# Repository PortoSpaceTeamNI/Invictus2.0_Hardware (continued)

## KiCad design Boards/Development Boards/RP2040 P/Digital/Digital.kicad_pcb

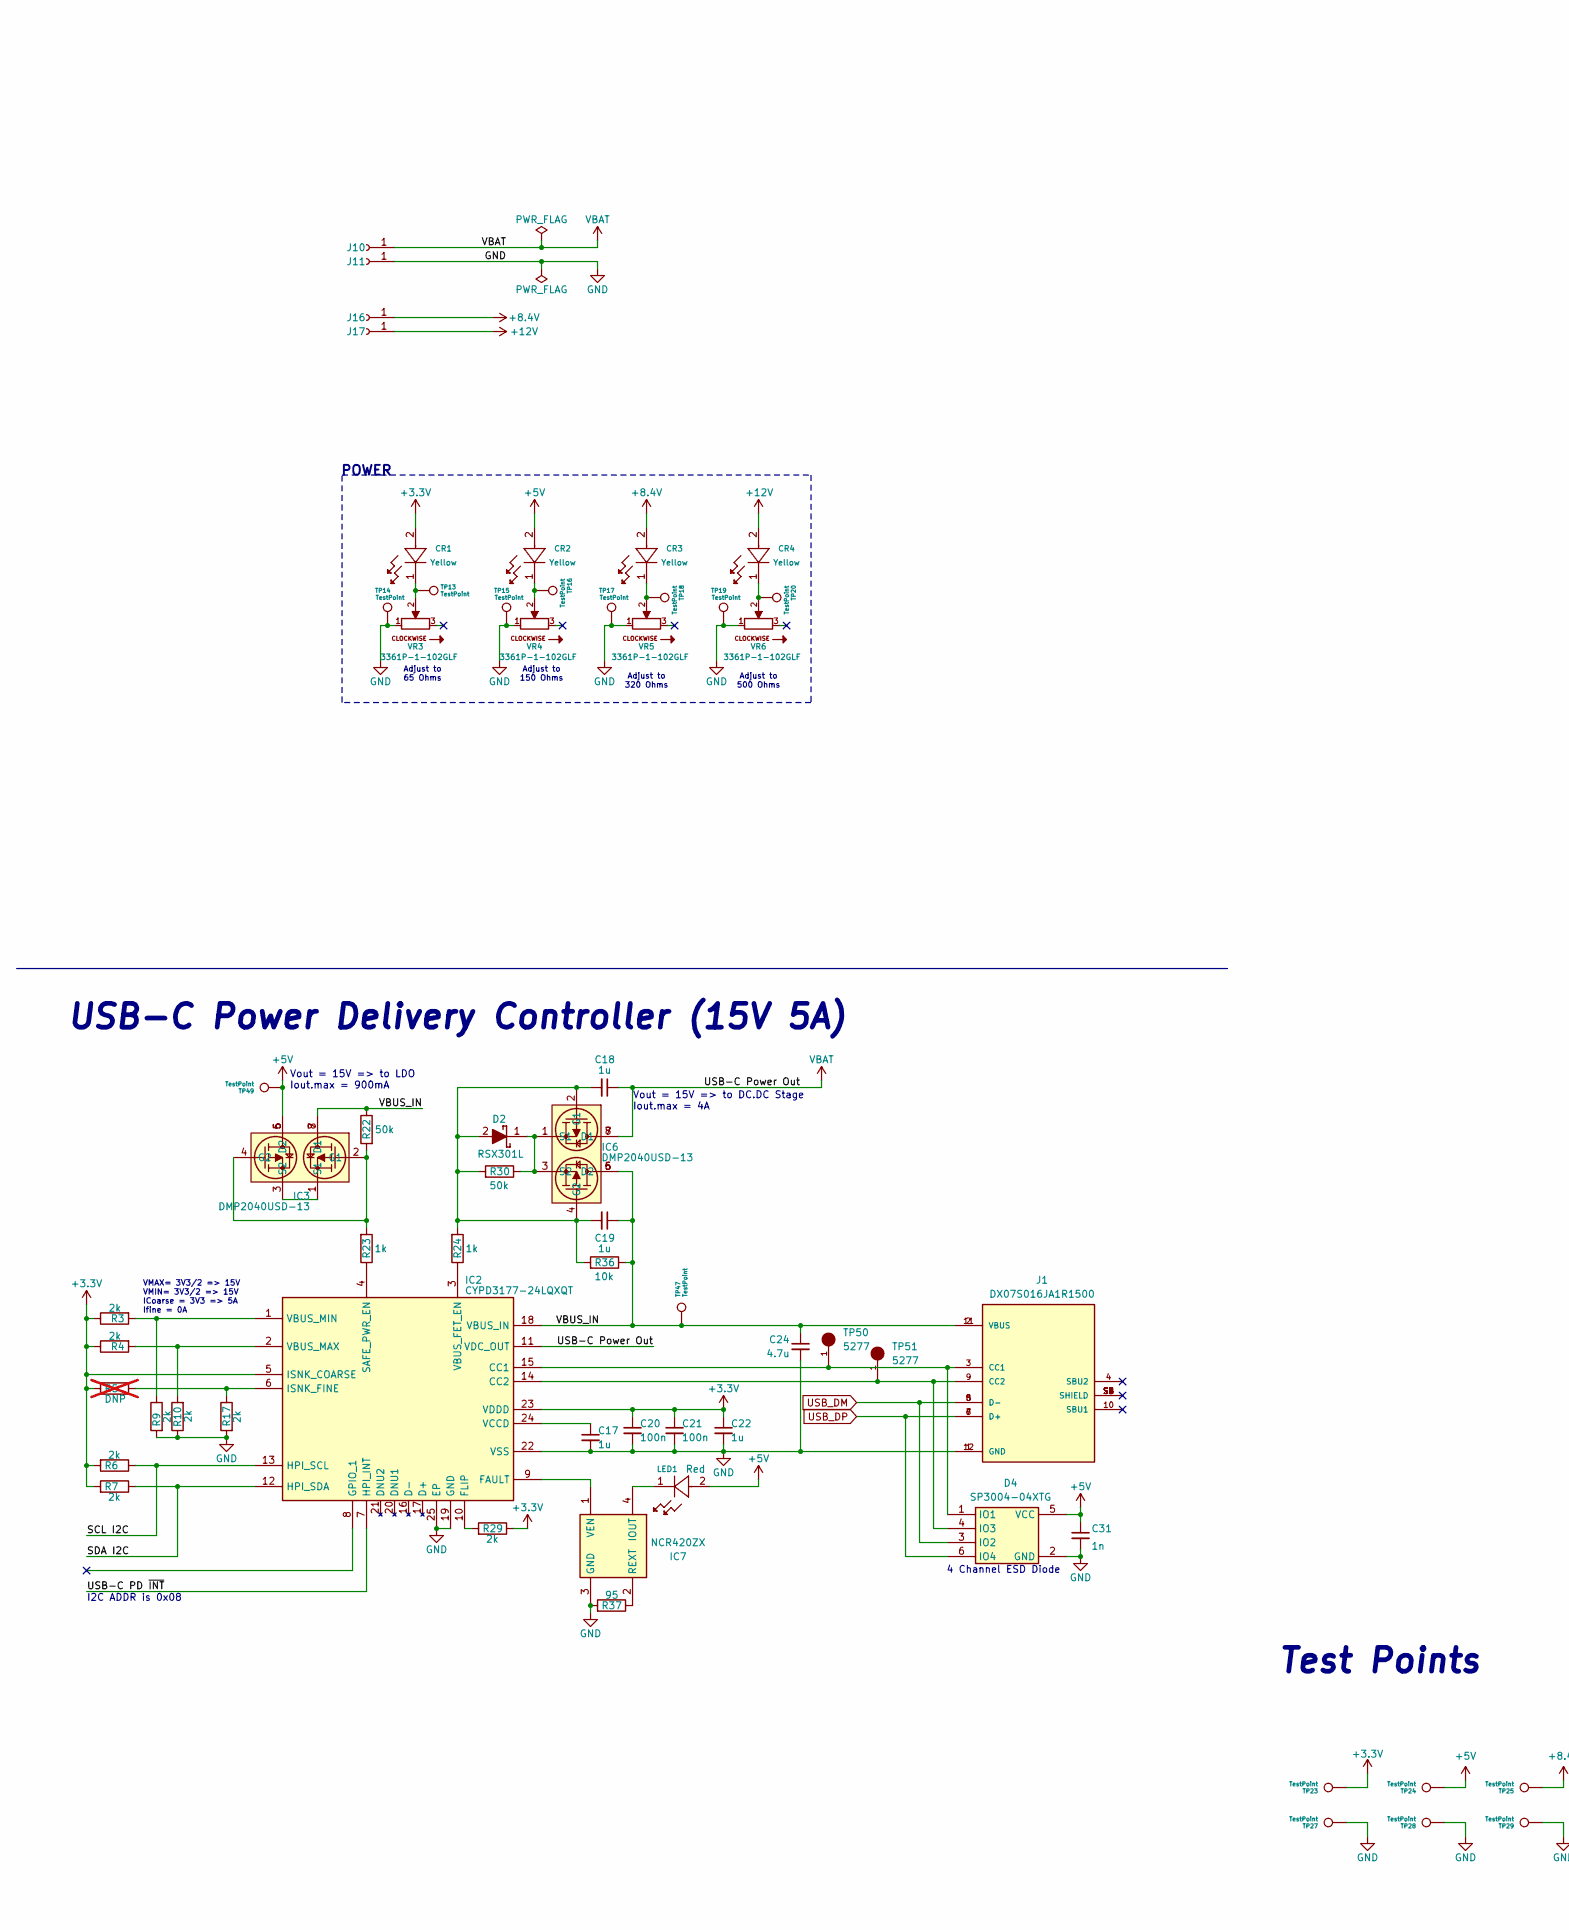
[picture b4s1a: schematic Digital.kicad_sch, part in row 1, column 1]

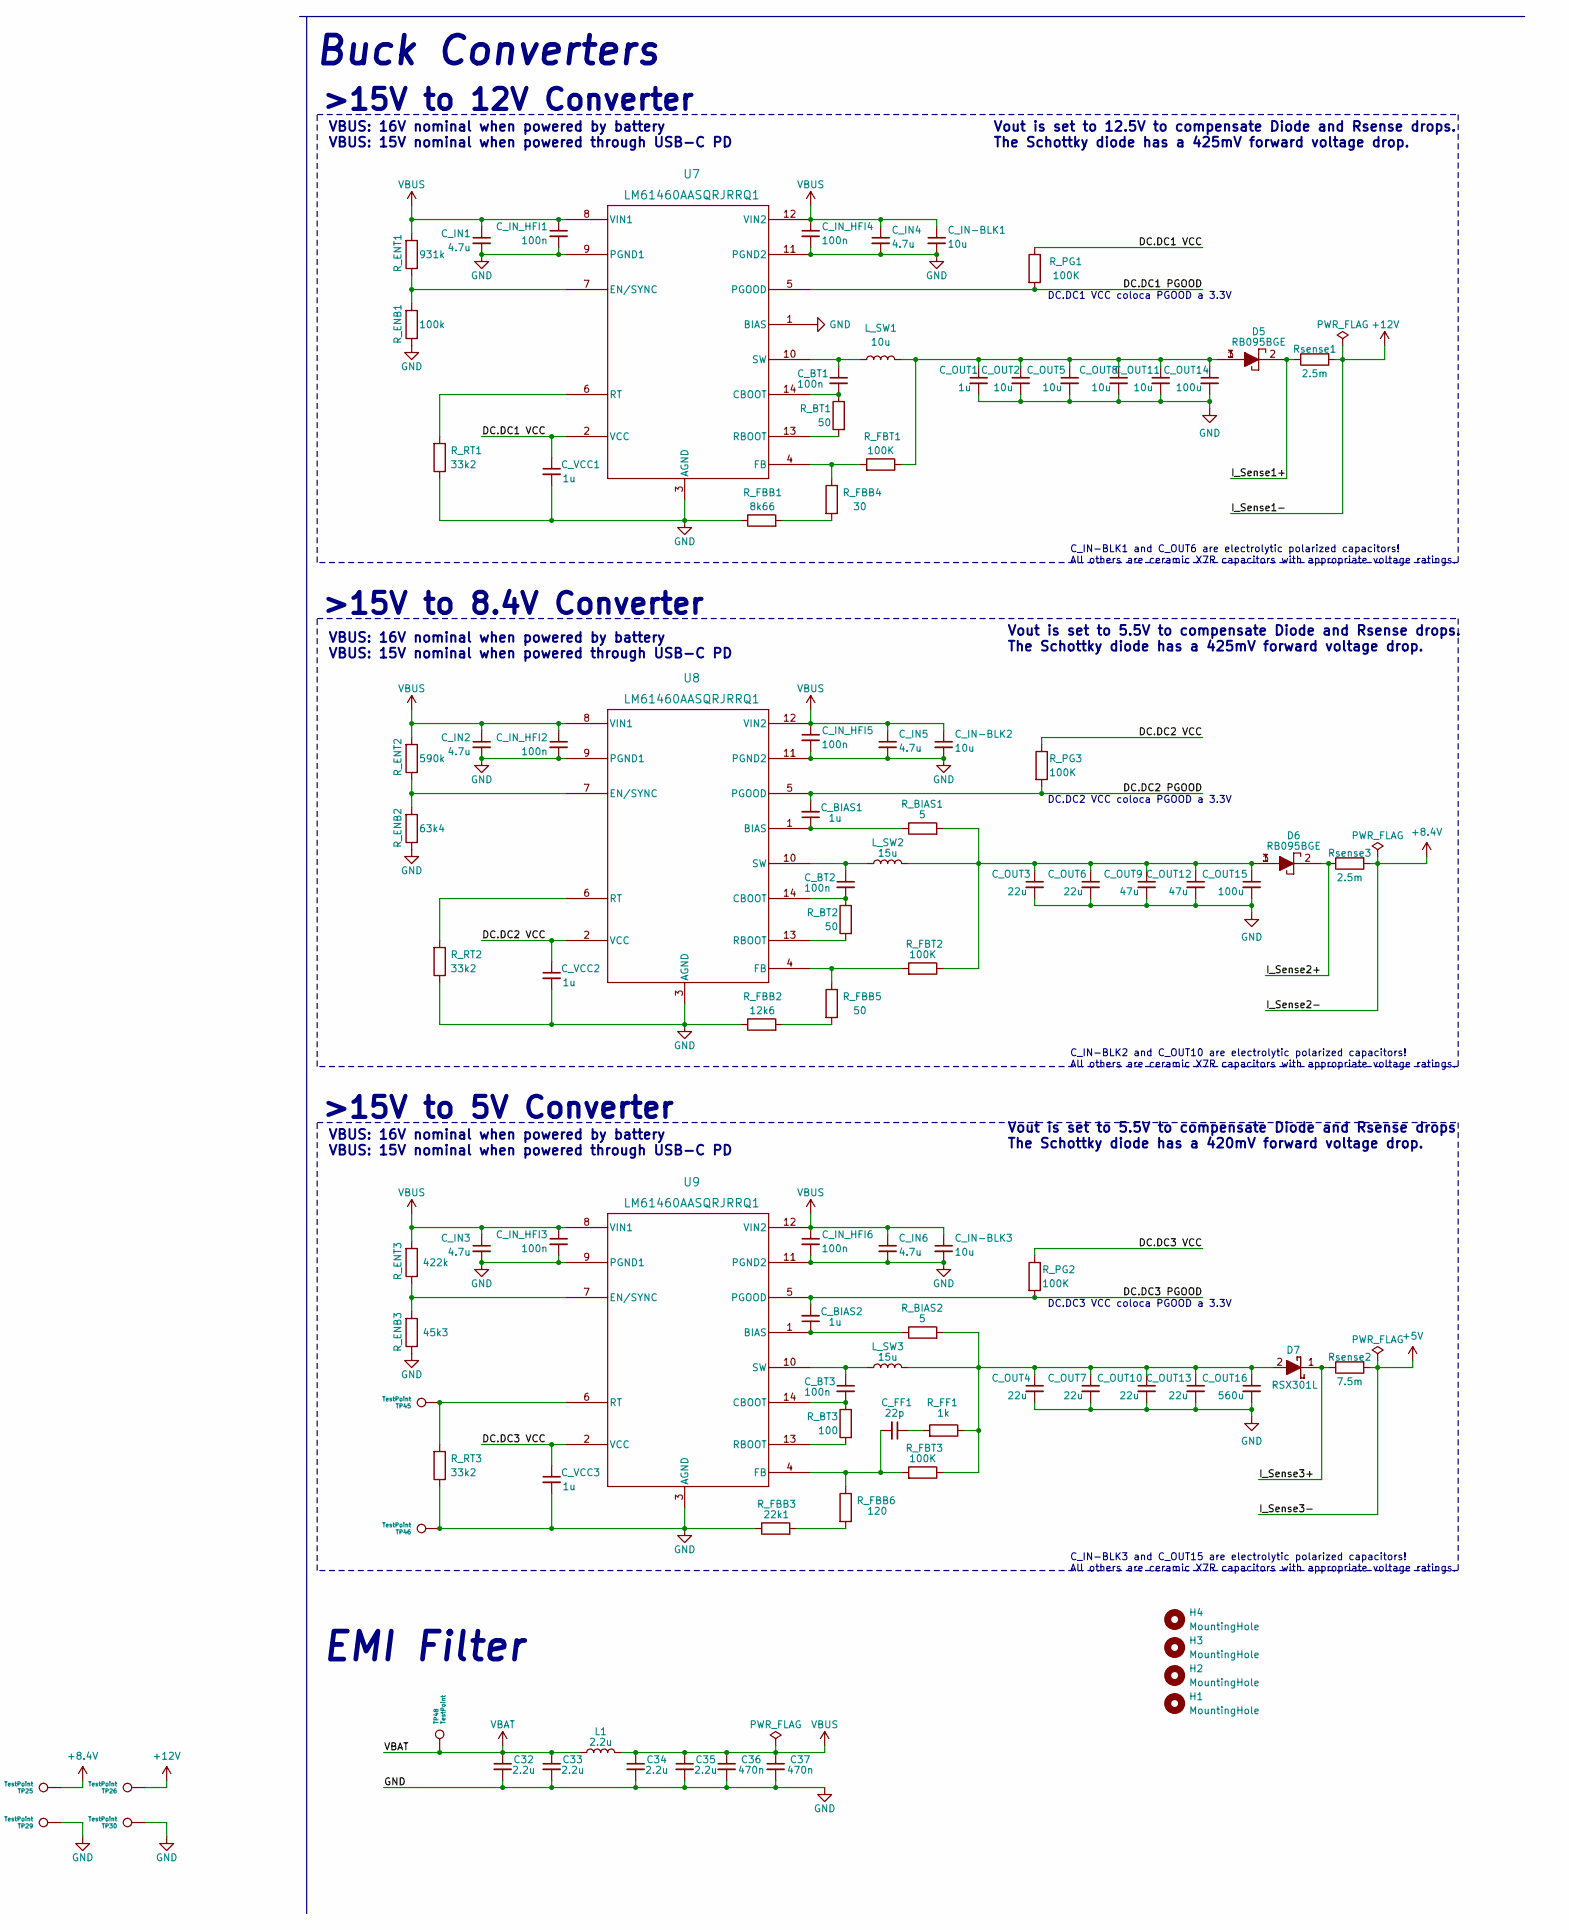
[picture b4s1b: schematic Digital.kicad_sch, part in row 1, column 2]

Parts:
C17, C18, C19, C22: 1u; Capacitor_0603
C20, C21: 100n; Capacitor_0402
C24: 4.7u; Capacitor_1206
C31: 1n; Capacitor_0402
C32, C33, C34, C35: 2.2u; Capacitor_0402
C36, C37: 470n; Capacitor_0402
CR1, CR2, CR3, CR4: VLMY1300-GS08; LEDC1608X100N
C_BIAS1, C_BIAS2: 1u; Capacitor_0603
C_BT1, C_BT2, C_BT3: 100n; Capacitor_0402
C_FF1: 22p; Capacitor_0402
C_IN1, C_IN2, C_IN3, C_IN4, C_IN5, C_IN6: 4.7u; Capacitor_1206
C_IN-BLK1, C_IN-BLK2, C_IN-BLK3: 10u; Capacitor_4mm
C_IN_HFI1, C_IN_HFI2, C_IN_HFI3, C_IN_HFI4, C_IN_HFI5, C_IN_HFI6: 100n; Capacitor_0402
C_OUT1: 1u; Capacitor_0603
C_OUT2, C_OUT5, C_OUT8, C_OUT11: 10u; Capacitor_0805
C_OUT3, C_OUT4, C_OUT6, C_OUT7, C_OUT10, C_OUT13: 22u; Capacitor_0805
C_OUT9, C_OUT12: 47u; Capacitor_0805
C_OUT14: 100u; Capacitor_6mm
C_OUT15: 100u; Capacitor_8mm
C_OUT16: 560u; Capacitor_8mm
C_VCC1, C_VCC2, C_VCC3: 1u; Capacitor_0603
D2, D7: RSX301L; DIOM5026X220N; Mouser Part Number 755-RSX301L-30DDTE25
D4: SP3004-04XTG; SOT563_LTF; Mouser Part Number 576-SP3004-04XTG
D5, D6: RB095BGE; RD3P175SNFRATL; Mouser Part Number 755-RB095BGE-30TL
H1, H2, H3, H4: MountingHole; MountingHole_3.2mm_M3_ISO7380_Pad_TopBottom
IC2: CYPD3177-24LQXQT; QFN50P400X400X60-25N-D; Mouser Part Number 727-CYPD3177-24LQXQT
IC3, IC6: DMP2040USD-13; SOIC127P600X175-8N; Mouser Part Number 621-DMP2040USD-13
IC7: NCR420ZX; SOT230P700X180-4N; Mouser Part Number 771-NCR420ZX
J1: DX07S016JA1R1500; JAE_DX07S016JA1R1500; PARTREV 1
J10, J11, J16, J17: Conn_01x01_Socket; Pico_01pin
L1: 2.2u; Inductor_10.1x10
LED1: VLMS1500-GS08; LED_00-GS08_VIS_RED
L_SW1: 10u; Inductor_11.5x10
L_SW2, L_SW3: 15u; Inductor_10.1x10
R3, R4, R6, R7, R9, R10, R17, R29: 2k; RES_0402
R5: DNP; RES_0402; not fitted
R22, R30: 50k; RES_0402
R23, R24: 1k; RES_0402
R36: 10k; RES_0402
R37: 95; RES_0402
R_BIAS1, R_BIAS2: 5; RES_0402
R_BT1, R_BT2: 50; RES_0402
R_BT3: 100; RES_0402
R_ENB1: 100k; RES_0603
R_ENB2: 63k4; RES_0402
R_ENB3: 45k3; RES_0402
R_ENT1: 931k; RES_0603
R_ENT2: 590k; RES_0402
R_ENT3: 422k; RES_0402
R_FBB1: 8k66; RES_0603
R_FBB2: 12k6; RES_0603
R_FBB3: 22k1; RES_0603
R_FBB4: 30; RES_0603
R_FBB5: 50; RES_0603
R_FBB6: 120; RES_0603
R_FBT1, R_FBT2, R_FBT3: 100K; RES_0603
R_FF1: 1k; RES_0402
R_PG1, R_PG2, R_PG3: 100K; RES_0603
R_RT1, R_RT2, R_RT3: 33k2; RES_0603
Rsense1, Rsense3: 2.5m; RES_0805
Rsense2: 7.5m; RES_WSLP2512
TP13, TP14, TP15, TP16, TP17, TP18, TP19, TP20, TP23, TP24, TP25, TP26, TP27, TP28, TP29, TP30: TestPoint; TestPoint_Pad_2.0x2.0mm
TP45, TP46, TP47, TP48, TP49: TestPoint; KEYSTONE_5277
TP50, TP51: 5277; KEYSTONE_5277
U7, U8, U9: LM61460AASQRJRRQ1; VQFN-HR14_RJR_TEX
VR3, VR4, VR5, VR6: 3361P-1-102GLF; TRIM_3361P-1-102GLF; PARTREV 08/19

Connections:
+3.3V: C20.1, C21.1, C22.1, CR1.2, IC2.5 (ISNK_COARSE), IC2.23 (VDDD), R3.1, R4.1, R5.2, R6.2, R7.2, R29.1, TP23.1; also elsewhere on the board
+5V: C31.1, CR2.2, D4.5 (VCC), IC3.5 (D2), IC3.6 (D2), LED1.2, Rsense2.2, TP24.1, TP49.1; also elsewhere on the board
+8.4V: CR3.2, J16.1, Rsense3.2, TP25.1
+12V: CR4.2, J17.1, Rsense1.2, TP26.1
/DC.DC1 PGOOD: R_PG1.2, U7.5 (PGOOD)
/DC.DC1 VCC: C_VCC1.1, R_PG1.1, U7.2 (VCC)
/DC.DC2 PGOOD: C_BIAS1.2, R_PG3.2, U8.5 (PGOOD)
/DC.DC2 VCC: C_VCC2.1, R_PG3.1, U8.2 (VCC)
/DC.DC3 PGOOD: C_BIAS2.2, R_PG2.2, U9.5 (PGOOD)
/DC.DC3 VCC: C_VCC3.1, R_PG2.1, U9.2 (VCC)
/I_Sense1+: D5.2, Rsense1.1
/I_Sense2+: D6.2, Rsense3.1
/I_Sense3+: D7.1 (K), Rsense2.1; also elsewhere on the board
/SCL I2C: IC2.13 (HPI_SCL), R6.1
/SDA I2C: IC2.12 (HPI_SDA), R7.1
/USB-C PD ~INT: IC2.7 (HPI_INT)
/VBUS_IN: C19.1, C24.1, IC2.18 (VBUS_IN), IC3.7 (D1), IC3.8 (D1), IC6.5 (D2), IC6.6 (D2), J1.2 (VBUS), J1.11 (VBUS), R22.1, R36.1, TP47.1
GND: C17.2, C20.2, C21.2, C22.2, C24.2, C31.2, C32.2, C33.2, C34.2, C35.2, C36.2, C37.2, C_IN1.2, C_IN2.2, C_IN3.2, C_IN4.2, C_IN5.2, C_IN6.2, C_IN-BLK1.2, C_IN-BLK2.2, C_IN-BLK3.2, C_IN_HFI1.2, C_IN_HFI2.2, C_IN_HFI3.2, C_IN_HFI4.2, C_IN_HFI5.2, C_IN_HFI6.2, C_OUT1.2, C_OUT2.2, C_OUT3.2, C_OUT4.2, C_OUT5.2, C_OUT6.2, C_OUT7.2, C_OUT8.2, C_OUT9.2, C_OUT10.2, C_OUT11.2, C_OUT12.2, C_OUT13.2, C_OUT14.2, C_OUT15.2, C_OUT16.2, C_VCC1.2, C_VCC2.2, C_VCC3.2, D4.2 (GND), IC2.19 (GND), IC2.22 (VSS), IC2.25 (EP), IC7.3 (GND), J1.1 (GND), J1.12 (GND), J11.1, R9.2, R10.1, R17.2, R37.2, R_ENB1.1, R_ENB2.1, R_ENB3.1, R_FBB1.1, R_FBB2.1, R_FBB3.1, R_RT1.1, R_RT2.1, R_RT3.1, TP14.1, TP15.1, TP17.1, TP19.1, TP27.1, TP28.1, TP29.1, TP30.1, TP46.1, U7.1 (BIAS), U7.3 (AGND), U7.9 (PGND1), U7.11 (PGND2), U8.3 (AGND), U8.9 (PGND1), U8.11 (PGND2), U9.3 (AGND), U9.9 (PGND1), U9.11 (PGND2), VR3.1, VR4.1, VR5.1, VR6.1; also elsewhere on the board
unnamed: CR1.1, TP13.1, VR3.2
unnamed: CR2.1, TP16.1, VR4.2
unnamed: CR3.1, TP18.1, VR5.2
unnamed: CR4.1, TP20.1, VR6.2
unnamed: C_FF1.1, R_FF1.2
unnamed: C_OUT1.1, C_OUT2.1, C_OUT5.1, C_OUT8.1, C_OUT11.1, C_OUT14.1, D5.1, D5.3, L_SW1.2, R_FBT1.1
unnamed: C_OUT3.1, C_OUT6.1, C_OUT9.1, C_OUT12.1, C_OUT15.1, D6.1, D6.3, L_SW2.2, R_BIAS1.2, R_FBT2.1
unnamed: C18.2, C19.2, D2.2 (A), IC6.2 (G1), IC6.4 (G2), R24.2, R30.2, R36.2
unnamed: D2.1 (K), IC6.1 (S1), IC6.3 (S2), R30.1
unnamed: D4.1 (IO1), IC2.15 (CC1), J1.3 (CC1), TP50.1
unnamed: D4.4 (IO3), IC2.14 (CC2), J1.9 (CC2), TP51.1
unnamed: C_OUT4.1, C_OUT7.1, C_OUT10.1, C_OUT13.1, C_OUT16.1, D7.2 (A), L_SW3.2, R_BIAS2.2, R_FBT3.1, R_FF1.1
unnamed: IC2.9 (FAULT), IC7.1 (VEN)
unnamed: IC2.10 (FLIP), R29.2
unnamed: IC2.6 (ISNK_FINE), R5.1, R17.1
unnamed: IC2.4 (SAFE_PWR_EN), R23.1
unnamed: IC2.3 (VBUS_FET_EN), R24.1
unnamed: IC2.2 (VBUS_MAX), R4.2, R10.2
unnamed: IC2.1 (VBUS_MIN), R3.2, R9.1
unnamed: C17.1, IC2.24 (VCCD)
unnamed: IC3.2 (G1), IC3.4 (G2), R22.2, R23.2
unnamed: IC3.1 (S1), IC3.3 (S2)
unnamed: IC7.4 (IOUT), LED1.1
unnamed: IC7.2 (REXT), R37.1
unnamed: R_FBB1.2, R_FBB4.2
unnamed: R_FBB2.2, R_FBB5.2
unnamed: R_FBB3.2, R_FBB6.2
unnamed: C_BT1.2, R_BT1.1, U7.14 (CBOOT)
unnamed: R_ENB1.2, R_ENT1.1, U7.7 (EN/SYNC)
unnamed: R_FBB4.1, R_FBT1.2, U7.4 (FB)
unnamed: R_BT1.2, U7.13 (RBOOT)
unnamed: R_RT1.2, U7.6 (RT)
unnamed: C_BT1.1, L_SW1.1, U7.10 (SW)
unnamed: C_BIAS1.1, R_BIAS1.1, U8.1 (BIAS)
unnamed: C_BT2.2, R_BT2.1, U8.14 (CBOOT)
unnamed: R_ENB2.2, R_ENT2.1, U8.7 (EN/SYNC)
unnamed: R_FBB5.1, R_FBT2.2, U8.4 (FB)
unnamed: R_BT2.2, U8.13 (RBOOT)
unnamed: R_RT2.2, U8.6 (RT)
unnamed: C_BT2.1, L_SW2.1, U8.10 (SW)
unnamed: C_BIAS2.1, R_BIAS2.1, U9.1 (BIAS)
unnamed: C_BT3.2, R_BT3.1, U9.14 (CBOOT)
unnamed: R_ENB3.2, R_ENT3.1, U9.7 (EN/SYNC)
unnamed: C_FF1.2, R_FBB6.1, R_FBT3.2, U9.4 (FB)
unnamed: R_BT3.2, U9.13 (RBOOT)
unnamed: R_RT3.2, TP45.1, U9.6 (RT)
unnamed: C_BT3.1, L_SW3.1, U9.10 (SW)
USB_DM: D4.3 (IO2), J1.5 (D-), J1.8 (D-)
USB_DP: D4.6 (IO4), J1.6 (D+), J1.7 (D+)
VBAT: C18.1, C32.1, C33.1, IC2.11 (VDC_OUT), IC6.7 (D1), IC6.8 (D1), J10.1, L1.1, TP48.1
VBUS: C34.1, C35.1, C36.1, C37.1, C_IN1.1, C_IN2.1, C_IN3.1, C_IN4.1, C_IN5.1, C_IN6.1, C_IN-BLK1.1, C_IN-BLK2.1, C_IN-BLK3.1, C_IN_HFI1.1, C_IN_HFI2.1, C_IN_HFI3.1, C_IN_HFI4.1, C_IN_HFI5.1, C_IN_HFI6.1, L1.2, R_ENT1.2, R_ENT2.2, R_ENT3.2, U7.8 (VIN1), U7.12 (VIN2), U8.8 (VIN1), U8.12 (VIN2), U9.8 (VIN1), U9.12 (VIN2)

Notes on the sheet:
4 Channel ESD Diode
Vout = 15V => to LDO Iout.max = 900mA
DC.DC3 VCC coloca PGOOD a 3.3V
Adjust to 320 Ohms
C_IN-BLK2 and C_OUT10 are electrolytic polarized capacitors! All others are ceramic X7R capacitors with appropriate voltage ratings.
C_IN-BLK1 and C_OUT6 are electrolytic polarized capacitors! All others are ceramic X7R capacitors with appropriate voltage ratings.
>15V to 5V Converter
>15V to 12V Converter
I2C ADDR is 0x08
Adjust to 150 Ohms
POWER
Vout is set to 5.5V to compensate Diode and Rsense drops The Schottky diode has a 420mV forward voltage drop.
VBUS: 16V nominal when powered by battery VBUS: 15V nominal when powered through USB-C PD
Vout is set to 5.5V to compensate Diode and Rsense drops. The Schottky diode has a 425mV forward voltage drop.
Test Points
>15V to 8.4V Converter
USB-C Power Delivery Controller (15V 5A)
Adjust to 65 Ohms
EMI Filter
Buck Converters
Vout = 15V => to DC.DC Stage Iout.max = 4A
DC.DC1 VCC coloca PGOOD a 3.3V
Vout is set to 12.5V to compensate Diode and Rsense drops. The Schottky diode has a 425mV forward voltage drop.
VMAX= 3V3/2 => 15V VMIN= 3V3/2 => 15V ICoarse = 3V3 => 5A Ifine = 0A
DC.DC2 VCC coloca PGOOD a 3.3V
Adjust to 500 Ohms
C_IN-BLK3 and C_OUT15 are electrolytic polarized capacitors! All others are ceramic X7R capacitors with appropriate voltage ratings.

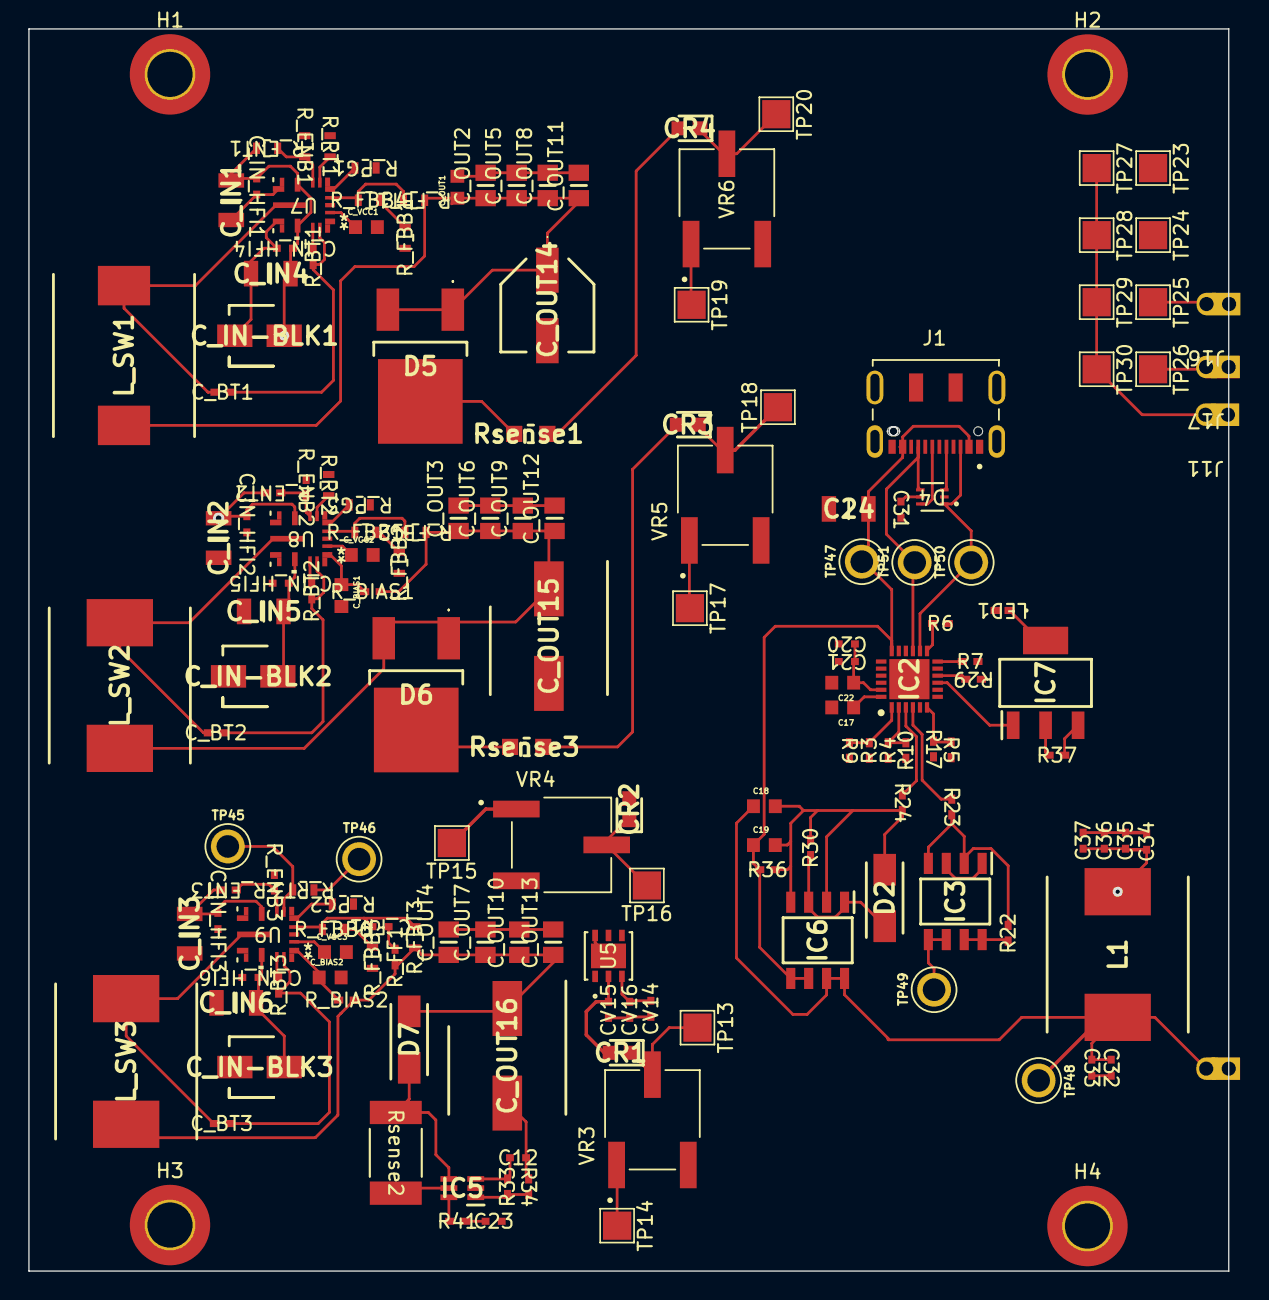
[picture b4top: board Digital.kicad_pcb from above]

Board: 6 copper layers, 85.0 x 88.0 mm, 166 parts (1 on the bottom side), 71 nets.

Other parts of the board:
C12, C23: 100n; Capacitor_0402
CV14, CV15: 4.7uF; Capacitor_0402
CV16: 1uF; Capacitor_0402
IC5: INA181A4QDCKRQ1; SOT65P210X110-6N
R33: 54k2; RES_0402
R34: 1k; RES_0402
R41: 160; RES_0402
U5: ST1L05APU33R; DFN_5APU33R_STM

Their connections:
+3.3V: C12.1, CV15.2, IC5.3 (VS), R33.2, U5.2 (V0); also elsewhere on the board
+5V: CV14.2, CV16.2, IC5.5 (IN-), U5.3 (V1); also elsewhere on the board
/5V_Sense: C23.1, R41.2
/I_Sense3+: IC5.4 (IN+); also elsewhere on the board
GND: C12.2, C23.2, CV14.1, CV15.1, CV16.1, IC5.2 (GND), R34.1, U5.6 (GND), U5.7 (GND); also elsewhere on the board
unnamed: IC5.6 (OUT), R41.1
unnamed: IC5.1 (REF), R33.1, R34.2
